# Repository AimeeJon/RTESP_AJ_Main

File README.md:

# RTESP_AJ_Main
Main folder for all real time embedded system programming work

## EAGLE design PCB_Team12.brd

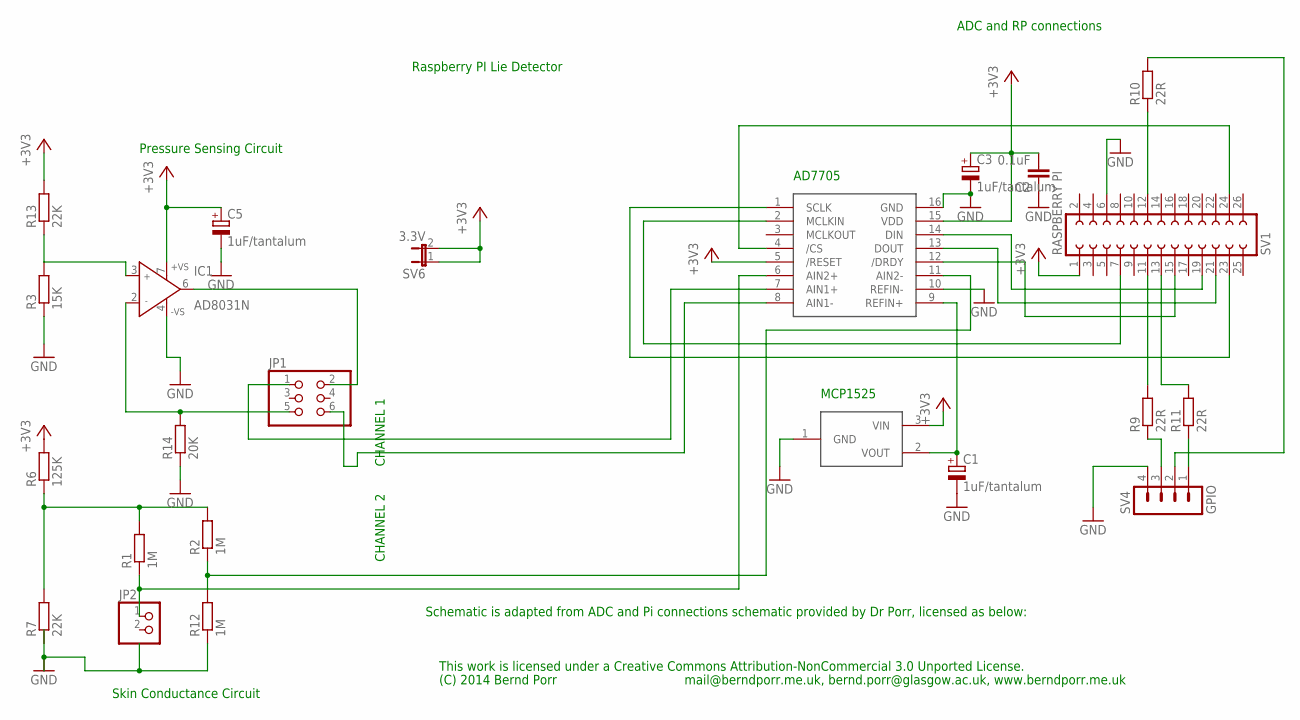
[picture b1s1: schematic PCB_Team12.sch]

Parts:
C1, C3, C5: 1uF/tantalum; TT2D7
C2: 0.1uF; C5B2.5
IC1: AD8031N; DIL08
JP1: PINHD-2X3; 2X03
JP2: PINHD-1X2; 1X02
R1, R2, R12: 1M; 0207/10
R3: 15K; 0207/10
R6: 125K; 0207/10
R7, R13: 22K; 0207/10
R9, R10, R11: 22R; 0207/10
R14: 20K; 0207/10
SV1: RASPBERRY PI; FE13-2
SV4: GPIO; MA04-1
SV6: 3.3V; JP1
U$1: AD7705; DIP16
U$2: MCP1525; TO92

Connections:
+3V3: C2.2, C3.+, C5.+, IC1.7 (+VS), R6.2, R13.2, SV1.1, SV6.1, SV6.2, U$1.5 (/RESET), U$1.15 (VDD), U$2.3 (VIN)
GND: C1.-, C2.1, C3.-, C5.-, IC1.4 (-VS), R3.1, R14.1, SV1.6, SV4.4, U$1.10 (REFIN-), U$1.16 (GND), U$2.1 (GND)
unnamed: SV1.19, U$1.14 (DIN)
unnamed: SV1.23, U$1.1 (SCLK)
unnamed: SV1.7, U$1.2 (MCLKIN)
unnamed: SV1.24, U$1.4 (/CS)
unnamed: C1.+, U$1.9 (REFIN+), U$2.2 (VOUT)
unnamed: SV1.21, U$1.13 (DOUT)
unnamed: IC1.2 (IN-), JP1.5, R14.2
unnamed: JP1.1, U$1.7 (AIN1+)
unnamed: R1.2, R2.2, R6.1, R7.2
unnamed: R9.2, SV1.11
unnamed: R10.1, SV1.12
unnamed: R11.2, SV1.13
unnamed: R9.1, SV4.3
unnamed: R11.1, SV4.1
unnamed: R10.2, SV4.2
unnamed: SV1.15, U$1.12 (/DRDY)
unnamed: IC1.3 (IN+), R3.2, R13.1
unnamed: R2.1, R12.2, U$1.11 (AIN2-)
unnamed: IC1.6 (OUT), JP1.2
unnamed: JP1.6, U$1.8 (AIN1-)
unnamed: JP2.1, R1.1, U$1.6 (AIN2+)

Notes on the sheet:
This work is licensed under a Creative Commons Attribution-NonCommercial 3.0 Unported License.
(C) 2014 Bernd Porr
mail@berndporr.me.uk, bernd.porr@glasgow.ac.uk, www.berndporr.me.uk
AD7705
MCP1525
CHANNEL 1
CHANNEL 2
Raspberry PI Lie Detector
Schematic is adapted from ADC and Pi connections schematic provided by Dr Porr, licensed as below:
Skin Conductance Circuit
Pressure Sensing Circuit
ADC and RP connections

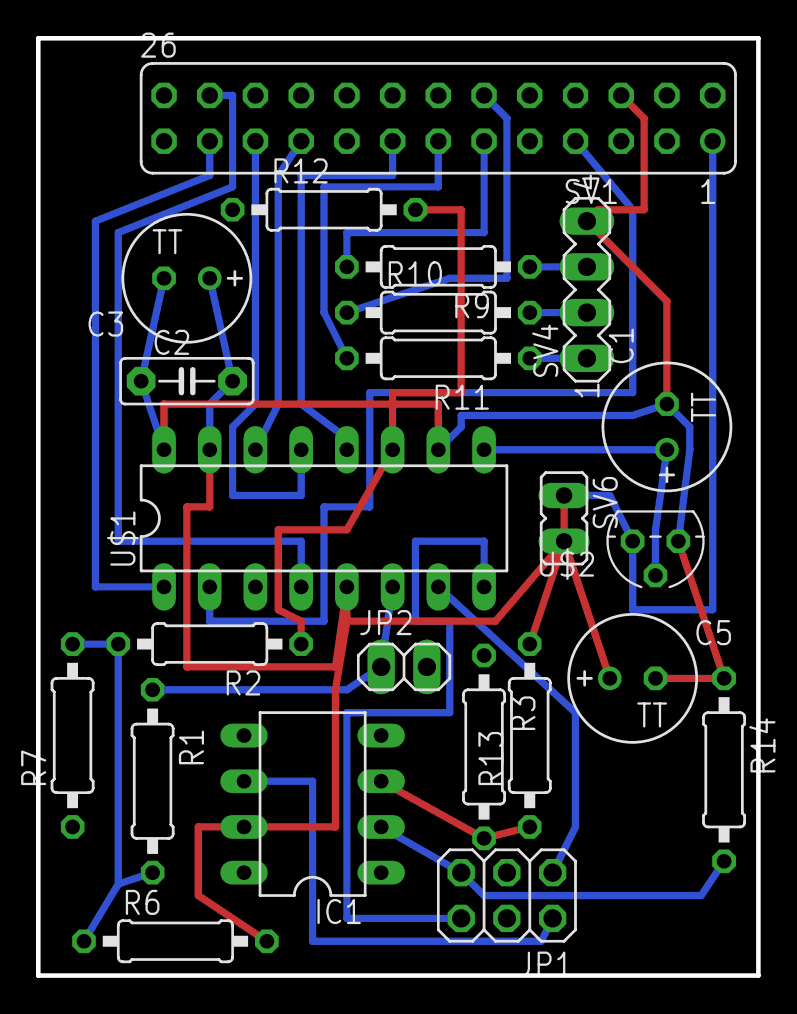
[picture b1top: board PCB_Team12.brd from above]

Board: 2 copper layers, 40.0 x 52.1 mm, 23 parts (0 on the bottom side), 23 nets.

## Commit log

2016-02-15 just a test commit
2016-02-15 Create testing updates
2016-04-17 Added files via upload
